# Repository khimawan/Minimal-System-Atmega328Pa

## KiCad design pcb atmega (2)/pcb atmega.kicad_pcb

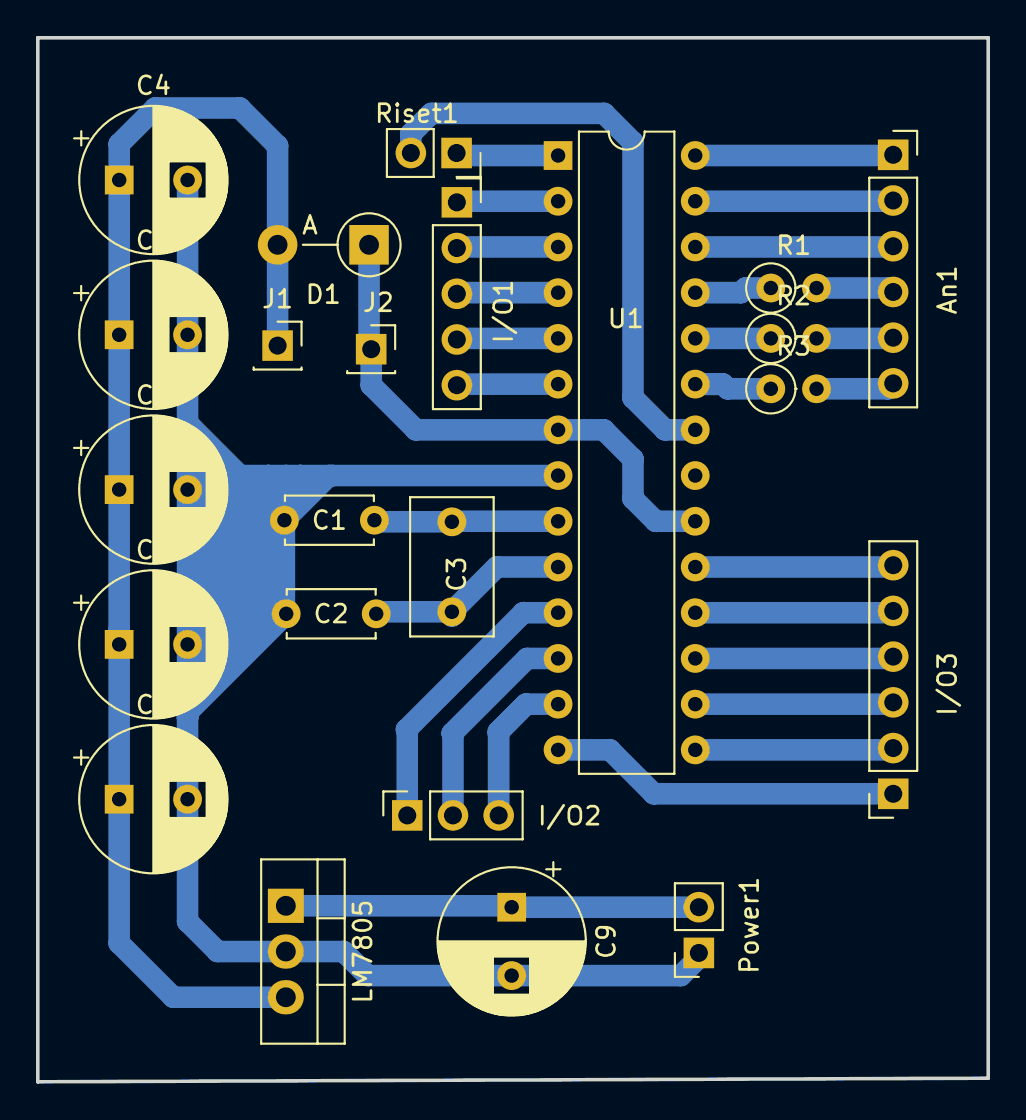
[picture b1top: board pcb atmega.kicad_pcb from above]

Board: 2 copper layers, 52.8 x 58.0 mm, 23 parts (0 on the bottom side), 30 nets.

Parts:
An1: Conn_01x06_Pin; PinSocket_1x06_P2.54mm_Vertical
C1, C2: C; C_Disc_D4.7mm_W2.5mm_P5.00mm
C3: C; C_Disc_D7.5mm_W4.4mm_P5.00mm
C4, C5, C6, C7, C8, C9: C; CP_Radial_D8.0mm_P3.80mm
D1: SB120; D_DO-41_SOD81_P5.08mm_Vertical_AnodeUp
I/O1: Conn_01x05_Pin; PinSocket_1x05_P2.54mm_Vertical
I/O2: Conn_01x03_Pin; PinSocket_1x03_P2.54mm_Vertical
I/O3: Conn_01x06_Pin; PinSocket_1x06_P2.54mm_Vertical
J1, J2: Conn_01x01_Pin; PinSocket_1x01_P2.54mm_Vertical
LM7805: LM7805_TO220; TO-220-3_Vertical
Power1: Conn_01x02_Pin; PinSocket_1x02_P2.54mm_Vertical
R1, R2, R3: 220; R_Axial_DIN0207_L6.3mm_D2.5mm_P2.54mm_Vertical
Riset1: Conn_01x02_Pin; PinSocket_1x02_P2.54mm_Vertical
U1: ATmega328-P; DIP-28_W7.62mm

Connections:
C1: C2.2, C3.2, U1.10 (XTAL2/PB7)
C2: C1.2, C3.1, U1.9 (XTAL1/PB6)
Earth: C1.1, C2.1, C4.2, C5.2, C6.2, C7.2, C8.2, C9.2, LM7805.2 (GND), Power1.1, Riset1.2, U1.8 (GND), U1.22 (GND)
unnamed: An1.1, U1.28 (PC5)
unnamed: An1.2, U1.27 (PC4)
unnamed: An1.3, U1.26 (PC3)
unnamed: An1.4, R1.2
unnamed: An1.5, R2.2
unnamed: An1.6, R3.2
unnamed: C4.1, C5.1, C6.1, C7.1, C8.1, D1.2 (A), J1.1, LM7805.3 (VO)
unnamed: I/O1.1, U1.2 (PD0)
unnamed: I/O1.2, U1.3 (PD1)
unnamed: I/O1.3, U1.4 (PD2)
unnamed: I/O1.4, U1.5 (PD3)
unnamed: I/O1.5, U1.6 (PD4)
unnamed: I/O2.1, U1.11 (PD5)
unnamed: I/O2.2, U1.12 (PD6)
unnamed: I/O2.3, U1.13 (PD7)
unnamed: I/O3.1, U1.14 (PB0)
unnamed: I/O3.2, U1.15 (PB1)
unnamed: I/O3.3, U1.16 (PB2)
unnamed: I/O3.4, U1.17 (PB3)
unnamed: I/O3.5, U1.18 (PB4)
unnamed: I/O3.6, U1.19 (PB5)
unnamed: C9.1, LM7805.1 (VI), Power1.2
unnamed: R3.1, U1.23 (PC0)
unnamed: R2.1, U1.24 (PC1)
unnamed: R1.1, U1.25 (PC2)
RST: Riset1.1, U1.1 (~RESET/PC6)
VCC: D1.1 (K), J2.1, U1.7 (VCC), U1.20 (AVCC)
